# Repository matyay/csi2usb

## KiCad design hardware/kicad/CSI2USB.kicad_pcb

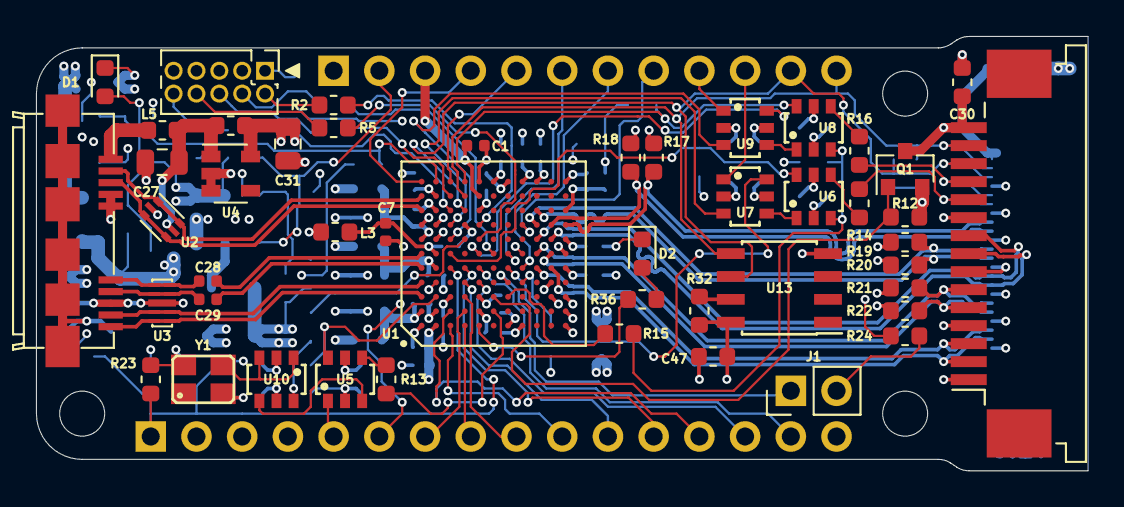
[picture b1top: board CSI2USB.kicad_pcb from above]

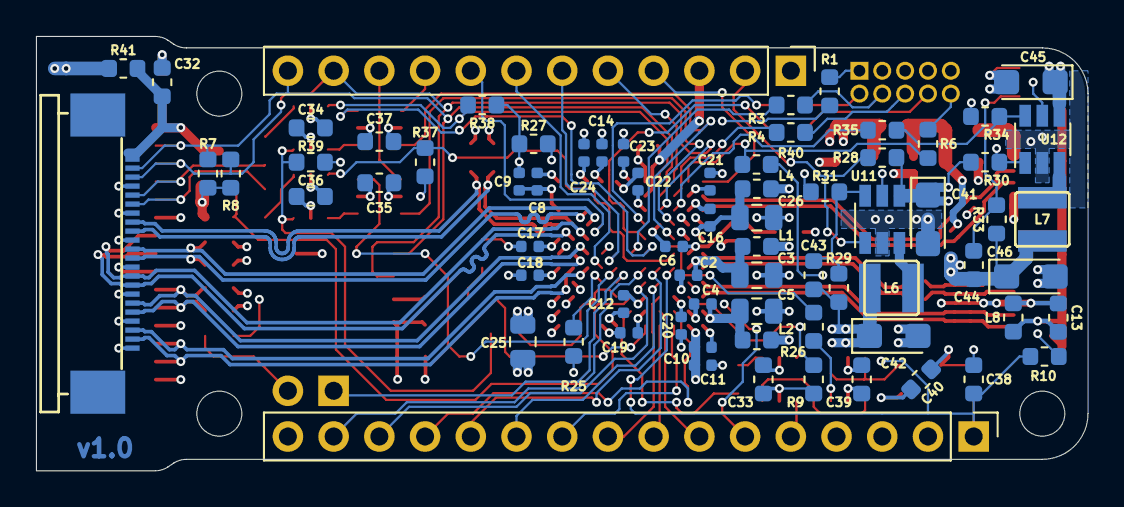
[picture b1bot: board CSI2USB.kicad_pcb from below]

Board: 4 copper layers, 58.4 x 24.1 mm, 119 parts (72 on the bottom side), 100 nets.

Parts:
C1, C2, C4, C7, C9, C11, C16, C28, C29: 100n; C_0402_1005Metric
C3, C5, C25: 22u; C_0805_2012Metric
C6, C8, C10, C12, C14, C17, C18, C19, C20, C21, C22, C23, C24: 10n; C_0402_1005Metric
C13, C30, C33, C34, C35, C36, C37, C38, C39, C40, C47: 100n; C_0603_1608Metric
C26: 2.2u; C_0805_2012Metric
C27, C31: 1u; C_0805_2012Metric
C32: 1u; C_0603_1608Metric
C41, C42, C45, C46: 22u; CP_EIA-3216-18_Kemet-A
C43, C44: 22p; C_0603_1608Metric
CON1: Conn_01x16; PinHeader_1x16_P2.54mm_Vertical
CON2: Conn_01x12; PinHeader_1x12_P2.54mm_Vertical
CON3: USB3_MICRO_B; Amphenol_GSB343133HR
CON4: Conn_01x22; MX-52435-2271
CON5: Conn_01x15; TE_1-84952-5_1x15-1MP_P1.0mm_Horizontal
CON6: Conn_02x05_Odd_Even; PinHeader_2x05_P1.27mm_Vertical
D1, D2: LED; LED_0603_1608Metric
J1: Conn_01x02; PinHeader_1x02_P2.54mm_Vertical
L1, L2, L3, L4, L5, L8: L; L_0603_1608Metric
L6, L7: 2.2u; DJNR3015
Q1: AO3401A; SOT-23
R1, R2, R3, R4, R5, R6, R13, R14, R15, R16, R26: 100R; R_0603_1608Metric
R7, R8, R9, R12, R23, R24, R25, R27, R29, R31, R37, R38, R39: 10k; R_0603_1608Metric
R10, R11, R32, R40, R41: 0R; R_0603_1608Metric
R17, R18, R19, R20, R21, R22, R28, R30: 100k; R_0603_1608Metric
R33: 15k; R_0603_1608Metric
R34: 3.3k; R_0603_1608Metric
R35, R36: 560R; R_0603_1608Metric
U1: CYUSB306X; BGA-121_11x11_10.0x10.0mm
U2: USBLC6-2P6; SOT-666
U3: SP3010-04UTG; uDFN-10
U4: NCP361; SOT-23-5
U5, U6, U7, U8, U9: 74LVC1G157; SC-74-6
U10: 74LVC2G17; SC-74-6
U11, U12: AP3402; TSOT-23-6
U13: M24M02; SOIC-8_3.9x4.9mm_P1.27mm
Y1: 19.2MHz; SMD_3.2x2.5

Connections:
+1V2: C17.1, C18.1, C19.1, C20.1, C21.1, C22.1, C23.1, C24.1, C25.1, C42.1, C43.1, L1.2, L2.2, L4.2, L6.2, R29.1, U1.B10, U1.C3, U1.E9, U1.F11, U1.H1, U1.J11, U1.L5, U1.L7
+3V3: C8.1, C9.1, C10.1, C11.1, C12.1, C14.1, C33.1, C34.1, C35.1, C36.1, C37.1, C39.1, C40.1, C44.1, C46.1, C47.1, CON1.2, L3.2, L7.2, Q1.2, R1.1, R7.1, R8.1, R12.2, R23.1, R24.1, R25.1, R32.1, R33.1, R41.1, U1.B1, U1.E3, U1.H11, U1.L9, U5.5, U6.5, U7.5, U8.5, U9.5, U10.5, U13.8, Y1.4
/CPU/CLKIN: R26.1, U1.D7
/CPU/LED1: R35.2, U1.C9
/CPU/LED2: R36.2, U1.E1
/CPU/TCK: R3.2, U1.F6
/CPU/TDI: R5.2, U1.E7
/CPU/TDO: R4.2, U1.C10
/CPU/TMS: R2.2, U1.E8
/CPU/~TRST: R6.2, R40.1, U1.B11
/MIPI/CAM_IO0: CON4.6, CON5.11, R14.2
/MIPI/CAM_IO1: CON4.5, CON5.12, R16.2
/MIPI/MCLK: R15.2, R39.2, U6.3, U8.3
/MIPI/MIPI_CLK_N: CON4.15, CON5.8, U1.K7
/MIPI/MIPI_CLK_P: CON4.14, CON5.9, U1.J7
/MIPI/MIPI_D0_N: CON4.21, CON5.2, U1.K5
/MIPI/MIPI_D0_P: CON4.20, CON5.3, U1.J5
/MIPI/MIPI_D1_N: CON4.18, CON5.5, R22.1, U1.K6
/MIPI/MIPI_D1_P: CON4.17, CON5.6, R21.1, U1.J6
/MIPI/MIPI_D2_N: CON4.12, R20.1, U1.J9
/MIPI/MIPI_D2_P: CON4.11, R19.1, U1.J8
/MIPI/MIPI_D3_N: CON4.9, R18.1, U1.K8
/MIPI/MIPI_D3_P: CON4.8, R17.1, U1.L8
/MIPI/REFCLK: R13.1, U1.F2
/MIPI/VCC_CAM: C30.1, C32.1, CON4.1, CON5.15, Q1.3, R41.2
/Power/AVDD: C16.1, C26.1, L4.1, U1.A7
/Power/CVDDQ: C6.1, C7.1, L3.1, U1.B6
/Power/U3RXVDDQ: C4.1, C5.1, L2.1, U1.A2
/Power/U3TXVDDQ: C2.1, C3.1, L1.1, U1.B5
/USB/USB_D_N: CON3.2, U1.A10, U2.1, U2.6
/USB/USB_D_P: CON3.3, U1.A9, U2.3, U2.4
/USB/USB_SSRX_N: CON3.9, U1.A4, U3.4, U3.7
/USB/USB_SSRX_P: CON3.10, U1.A3, U3.5, U3.6
/USB/USB_SSTX_AC_N: C28.2, CON3.6, U3.1, U3.10
/USB/USB_SSTX_AC_P: C29.2, CON3.7, U3.2, U3.9
/USB/USB_SSTX_N: C28.1, U1.A6
/USB/USB_SSTX_P: C29.1, U1.A5
CAM_IO0_EXT: CON2.10, U7.1
CAM_IO0_GPIO: U1.C8, U7.3
CAM_IO0_SEL0: U1.G5, U7.6
CAM_IO0_SEL1: R37.2, U1.C6, U6.6
CAM_IO1_EXT: CON2.9, U9.1
CAM_IO1_GPIO: U1.C7, U9.3
CAM_IO1_SEL0: U1.E6, U9.6
CAM_IO1_SEL1: R38.2, U1.D11, U8.6
CAM_PWREN: Q1.1, R12.1, U1.F3
CLK_19.2M: U5.3, U10.4
EXT_PWREN: CON2.2, R28.1, U11.1
GND: C1.2, C2.2, C3.2, C4.2, C5.2, C6.2, C7.2, C8.2, C9.2, C10.2, C11.2, C12.2, C13.1, C14.2, C16.2, C17.2, C18.2, C19.2, C20.2, C21.2, C22.2, C23.2, C24.2, C25.2, C26.2, C27.1, C30.2, C31.1, C32.2, C33.2, C34.2, C35.2, C36.2, C37.2, C38.2, C39.2, C40.2, C41.2, C42.2, C45.2, C46.2, C47.2, CON1.4, CON3.4, CON3.5, CON3.8, CON4.4, CON4.7, CON4.10, CON4.13, CON4.16, CON4.19, CON4.22, CON5.1, CON5.4, CON5.7, CON5.10, CON6.3, CON6.5, CON6.9, D1.1, D2.1, L8.2, R9.1, R17.2, R18.2, R19.2, R20.2, R21.2, R22.2, R27.2, R31.2, R34.2, R37.1, R38.1, R39.1, U1.A1, U1.A8, U1.B2, U1.B7, U1.B8, U1.B9, U1.D8, U1.E2, U1.E11, U1.G1, U1.G11, U1.K3, U1.K4, U1.L1, U1.L2, U1.L3, U1.L6, U1.L11, U2.2, U3.3, U3.8, U4.2, U4.3, U5.2, U6.2, U7.2, U8.2, U9.2, U10.2, U11.2, U12.2, U13.4, Y1.2
GPIO21: CON1.6, U1.B4
GPIO24: CON2.4, U1.A11
I2C_SCL: CON2.11, CON4.3, CON5.13, R8.2, U1.D9, U13.6
I2C_SDA: CON2.12, CON4.2, CON5.14, R7.2, U1.D10, U13.5
I2S_CLK: CON1.8, U1.D1
I2S_MCLK: CON2.5, U1.C11
I2S_SD: CON1.7, U1.D2
I2S_WS: CON1.9, U1.D3
MIPI_HSYNC: CON2.6, U1.G6
MIPI_PCLK: CON2.8, U1.H8
MIPI_REFCLK_EXT: CON1.5, U5.1
MIPI_REFCLK_SEL: R9.2, U1.B3, U5.6
MIPI_VSYNC: CON2.7, U1.H5
unnamed: C13.2, CON3.11, L8.1
unnamed: C27.2, L5.2, R11.2, U2.5, U4.1
unnamed: C43.2, R29.2, R31.1, U11.6
unnamed: C44.2, R33.2, R34.1, U12.6
unnamed: CON3.1, L5.1
unnamed: CON6.1, R1.2
unnamed: CON6.2, R2.1
unnamed: CON6.4, R3.1
unnamed: CON6.6, R4.1
unnamed: CON6.8, R5.1
unnamed: CON6.10, R6.1
unnamed: D1.2, R35.1
unnamed: D2.2, R36.1
unnamed: J1.1, U1.G4
unnamed: J1.2, R24.2
unnamed: L6.1, U11.3
unnamed: L7.1, U12.3
unnamed: R10.1, U12.5
unnamed: R13.2, U5.4
unnamed: R14.1, U6.4
unnamed: R15.1, U1.G3
unnamed: R16.1, U8.4
unnamed: R25.2, U1.H4
unnamed: R26.2, U10.6
unnamed: R27.1, U1.H6
unnamed: R30.1, U11.5, U12.1
unnamed: R32.2, U13.7
unnamed: U6.1, U7.4
unnamed: U8.1, U9.4
unnamed: U10.1, U10.3, Y1.3
SPI_MISO: CON1.13, U1.C2
SPI_MOSI: CON1.12, U1.D5
SPI_SCK: CON1.11, U1.D4
SPI_SS: CON1.10, U1.C1
UART_RXD: CON1.14, U1.E4
UART_TXD: CON1.15, U1.E5
VBUS: C1.1, C31.2, C41.1, C45.1, CON2.3, R11.1, R28.2, R30.2, U1.E10, U4.5, U11.4, U12.4
~RESET: C38.1, CON1.1, R10.2, R23.2, R40.2, U1.C5

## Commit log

2020-06-21 Added KiCad project
2020-06-21 Addded PCB render files
